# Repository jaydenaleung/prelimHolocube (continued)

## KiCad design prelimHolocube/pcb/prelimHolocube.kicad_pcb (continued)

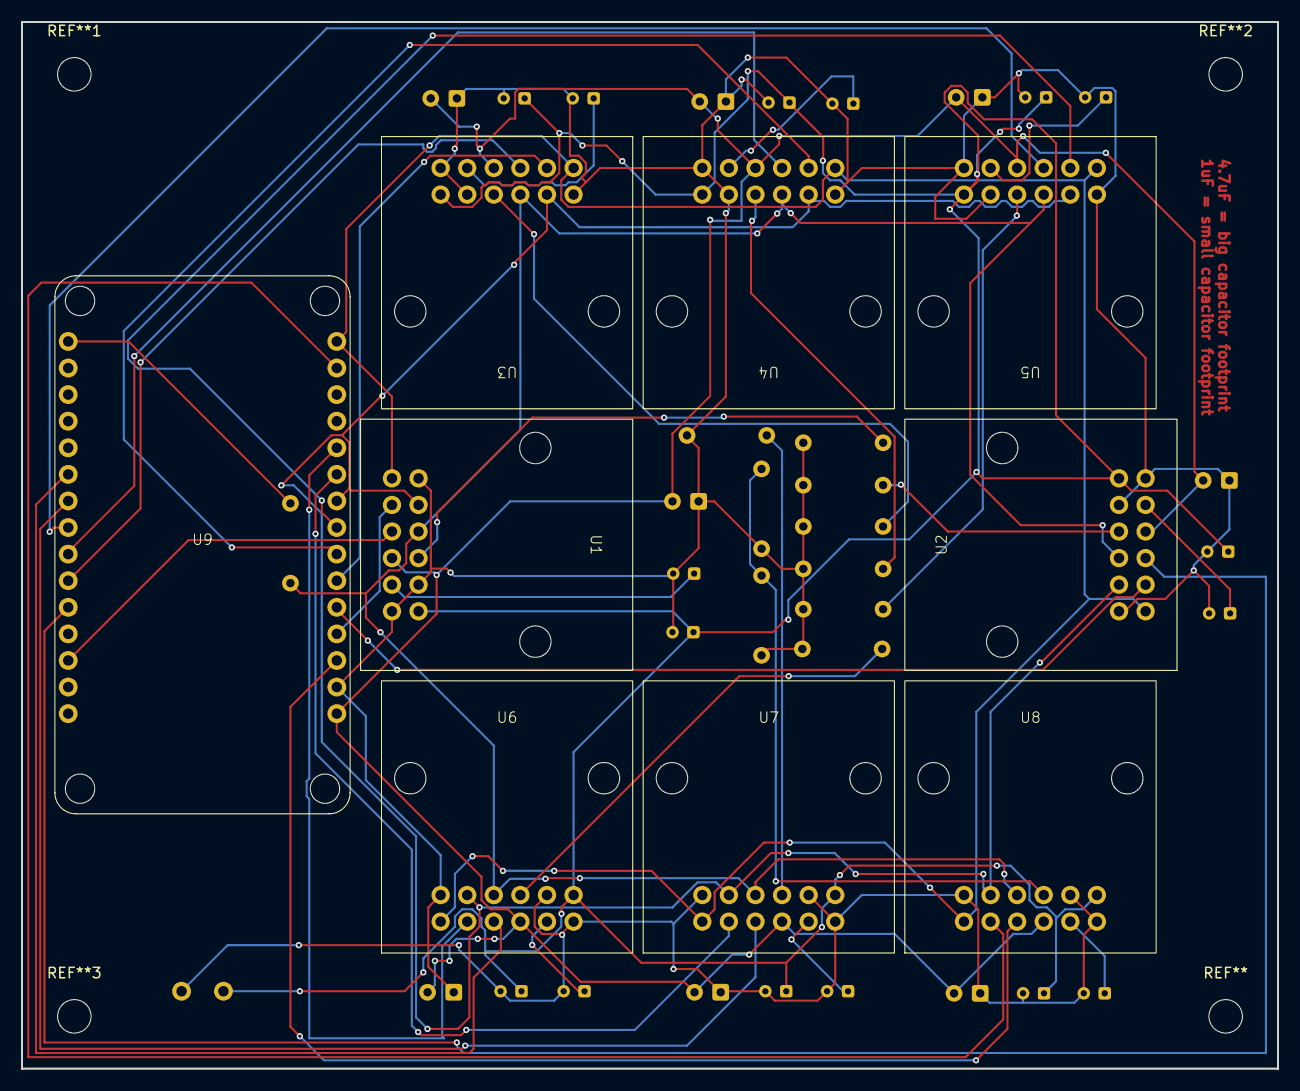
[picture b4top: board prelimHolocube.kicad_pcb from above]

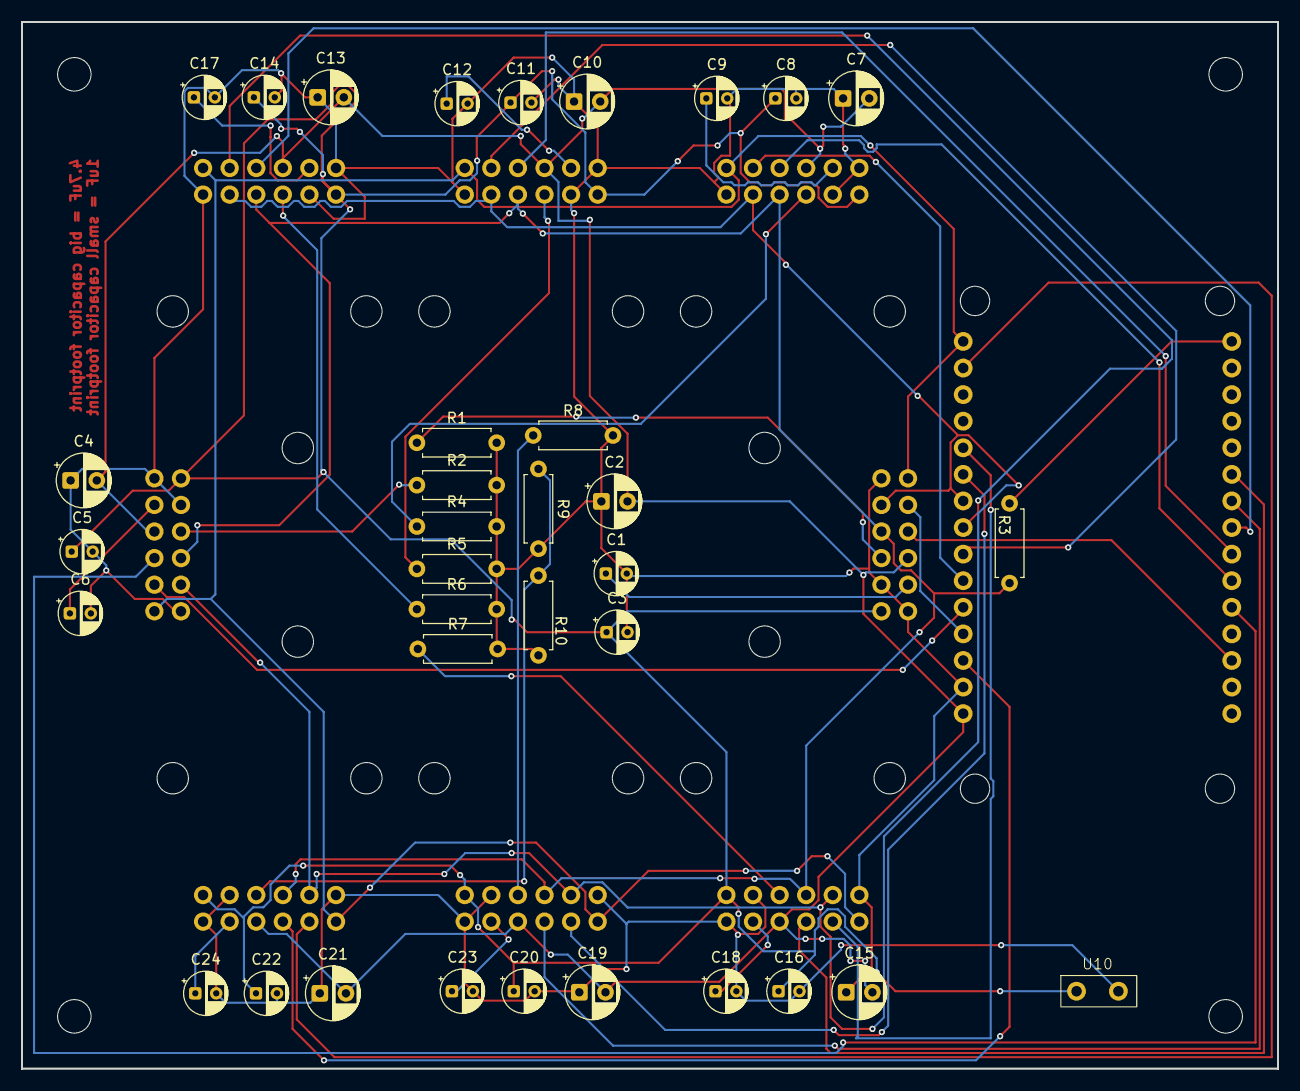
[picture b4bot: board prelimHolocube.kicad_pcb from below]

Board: 2 copper layers, 120.0 x 100.0 mm, 44 parts (35 on the bottom side), 39 nets.

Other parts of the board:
R10: 1M; R_Axial_DIN0207_L6.3mm_D2.5mm_P7.62mm_Horizontal

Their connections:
GND: R10.2; also elsewhere on the board
unnamed 33: R10.1; also elsewhere on the board

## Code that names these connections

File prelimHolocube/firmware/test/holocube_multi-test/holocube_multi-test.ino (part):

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//  2  SI     -> GPIO23 (VSPI MOSI)
//  3  SCL    -> GPIO18 (VSPI SCK)
//  4  A0/DC  -> GPIO16 (RX2) (any GPIO; can be SHARED by all 8 panels later)
//  5  RES    -> GPIO4  (MUST be a GPIO - do NOT tie to ESP32 EN pin)
//  6  CS     -> GPIO17 (TX2) (unique per panel)
//  7  IREF   -> 1M 1% resistor to GND
//  8  VDD    -> 3.3V (ESP32 3V3), 1uF ceramic to GND at the pin
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// 12  VSS    -> GND
//
// Power-up order (datasheet p.15): VDD+VPP on while RES held low >=10us,
// then RES high, init, 0xAF. u8g2 handles this if RES is on a GPIO.
// Power-down: display off / VPP off first, then VDD (~100ms later).
// -----------------------------------------------------------------

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   pulses RES and sends DISPLAY ON (0xAF). With VDD+VPP present and a
   good FPC connection, the panel MUST show random pixels/speckle
   (RAM is uninitialized). If it stays fully dark, the problem is
   hardware: FPC orientation/pin order, VPP, RES, or ground.
*/


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// //  SI   (MOSI)   -> GPIO23 (D23)       shared by all panels (VSPI MOSI)
// //  SCL  (SCK)    -> GPIO18 (D18)       shared by all panels (VSPI SCK)
// //  A0   (DC)     -> GPIO16 (RX2)       shared by all panels
// //  RES           -> GPIO17 (TX2)       shared by all panels, 10k pull-up (R2)
// //  CS_1          -> GPIO13 (D13)       10k pull-up (R3)
// //  CS_2          -> GPIO14 (D14)       10k pull-up (R5)
// //  CS_3          -> GPIO27 (D27)       10k pull-up (R6)
// //  CS_4          -> GPIO26 (D26)       10k pull-up (R8)
// //  CS_5          -> GPIO25 (D25)       10k pull-up (R9)
// //  CS_6          -> GPIO33 (D33)       10k pull-up (R11)
// //  CS_7          -> GPIO32 (D32)       10k pull-up (R12)
// //  CS_8          -> GPIO4  (D4)        10k pull-up (R14)
// //
// // Per-panel FPC pin -> signal
// //  1  VSS    -> GND (common with VPP supply ground AND USB ground!)
// //  2  SI     -> SI bus
// //  3  SCL    -> SCL bus
// //  4  A0/DC  -> A0 bus
// //  5  RES    -> RES bus (MUST be a GPIO - do NOT tie to ESP32 EN pin)
// //  6  CS     -> CS_n (unique per panel)
// //  7  IREF   -> 1M 1% resistor to GND
// //  8  VDD    -> 3.3V (ESP32 3V3), 1uF ceramic to GND at the pin
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//    u8g2 code. It pulses the shared RES once and sends DISPLAY ON to every
//    panel with 0xA5 (entire display ON), so every panel with VDD+VPP and a
//    good FPC connection MUST glow fully. A dark panel is hardware: FPC
//    orientation/pin order, VPP, RES, CS, or ground.
// */


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
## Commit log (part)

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2025-10-04 init
2025-10-13 finish pcb
2025-10-13 add cad model and mounting holes
2025-12-21 switched to holo's prelimHolocube using this as a reference, deleted tracks to flip footprint, need to reroute
2026-06-26 Add 38pin pinout
